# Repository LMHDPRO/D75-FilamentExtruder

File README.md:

<div align="center">

```
██████╗  ██████╗ ██╗   ██╗ ██████╗ ██╗      █████╗ ███████╗███╗███████╗
██╔══██╗██╔═══██╗██║   ██║██╔════╝ ██║     ██╔══██╗██╔════╝ ██║██╔════╝
██║  ██║██║   ██║██║   ██║██║  ███╗██║     ███████║███████╗╚██║███████╗
██║  ██║██║   ██║██║   ██║██║   ██║██║     ██╔══██║╚════██║ ██║╚════██║
██████╔╝╚██████╔╝╚██████╔╝╚██████╔╝███████╗██║  ██║███████║ ██║███████║
╚═════╝  ╚═════╝  ╚═════╝  ╚═════╝ ╚══════╝╚═╝  ╚═╝╚══════╝ ╚═╝╚══════╝
```

# Filament Extruder Controller

**ESP32 DualCore · FreeRTOS · PID Temperature · Dual TB6600**

*Reduce PP filament — 2.4 mm → 1.75 mm for 3D printing*

---

</div>

---

## ¿Qué es esto?

**Douglas75** es un controlador open-source para una extrusora de filamento, desarrollado originalmente en el marco de un **Practicum** universitario para reducir el diámetro de filamento fabricado artesanalmente. El diseño nació con polipropileno (PP) de **2.4 mm → 1.75 mm**, pero el sistema es compatible con cualquier tipo de filamento termoplástico que requiera un proceso de reducción controlada de diámetro.

El sistema corre en un **ESP32 con FreeRTOS dual-core** — un núcleo dedicado al control PID de temperatura y otro a la interfaz de usuario. Incluye un **panel de control Tkinter** para operación desde PC vía USB serial.

---

## Características

| | Función | Detalle |
|---|---|---|
| 🌡️ | Control temperatura | PID con NTC 100K genérico Ender3 (β = 3950) |
| 🔥 | Calefactor | MOSFET IRLZ44N, PWM 5 kHz vía LEDC |
| 💨 | Ventilador | MOSFET IRLZ44N, PWM proporcional AUTO o manual OFF |
| ⚙️ | Motores | 2× NEMA17 full-step, drivers TB6600, enable compartido |
| 🖥️ | LCD | I2C 20×4 @ 0x27, menú completo con encoder KY-040 |
| 💻 | GUI PC | Tkinter dark mode + gráfica temperatura en tiempo real |
| 🧵 | Estimación | Contador de filamento procesado (mm y gramos) |
| ⚡ | Arquitectura | FreeRTOS — Core 0: PID · Core 1: HMI |

---

## Hardware

### Bill of Materials (BOM)

| # | Categoría | Componente | Modelo / Especificación | Qty |
|:---:|---|---|---|:---:|
| 1 | 🧠 MCU | Microcontrolador | ESP32 Development Board | 1 |
| 2 | 🔥 Calefactor | Hotend completo | 40W 12V Ceramic Cartridge Heater + NTC 100K Thermistor | 1 |
| 3 | 🔩 Boquilla | Nozzle | MK8 0.4 mm Nozzle | 1 |
| 4 | ⚙️ Extrusión | Extrusor | Creality MK8 Extruder | 1 |
| 5 | ⚙️ Motor | Motor paso a paso | NEMA17 Stepper Motor | 2 |
| 6 | ⚙️ Driver | Driver motor | TB6600 Stepper Motor Driver | 2 |
| 7 | 🔧 Soporte | Montura motor | NEMA Motor Mount | 2 |
| 8 | 🖥️ Pantalla | Pantalla LCD | 20×4 LCD Screen I2C | 1 |
| 9 | 🎛️ Entrada | Encoder rotatorio | KY-040 Rotary Encoder | 1 |
| 10 | 🧵 Sensor | Sensor de filamento | Filament Runout Sensor | 1 |
| 11 | ⚡ Regulador | Regulador voltaje | L7805CV 5V Voltage Regulator (TO-220) | 1 |
| 12 | ⚡ MOSFET | MOSFET N-Channel | IRFL44N N-Channel MOSFET | 2 |
| 13 | 🔩 Rodamientos | Rodamiento | 608ZZ Bearing | 4 |
| 14 | 💨 Ventilador | Fan | 4010 Fan 12V | 1 |
| 15 | 🟫 PCB | Placa base | 15×15 cm Single-Sided Phenolic Board | 1 |
| 16 | 🔌 Conectores | Pin header | 36-pin Single Row Pin Header (2.54 mm) | 1 |
| 17 | 🔌 Conectores | Female header | 10-pin Female Header (2.54 mm) | 2 |
| 18 | 🔌 Conectores | Terminales | 2-Pin Green Screw Terminals | 6 |
| 19 | 🔋 Capacitores | Condensador electrolítico | 100 µF | 2 |
| 20 | 🔋 Capacitores | Condensador cerámico | 100 nF | 2 |
| 21 | 🔩 Tornillería | Tornillos Allen | M2, M3 & M4 Socket Head Screws (surtido) | — |

### Mapa de pines ESP32

| GPIO | Señal | Tipo |
|---|---|---|
| `18` | OUTA encoder (CLK) | Input interrupt |
| `19` | OUTB encoder (DT) | Input interrupt |
| `5` | SW encoder | Input PULLUP |
| `34` | Termistor NTC | ADC1_CH6 |
| `25` | MOSFET calefactor | PWM LEDC ch0 |
| `23` | MOSFET ventilador | PWM LEDC ch1 |
| `26` | STEP Motor 1 | Output |
| `27` | DIR Motor 1 | Output |
| `4` | STEP Motor 2 | Output |
| `2` | DIR Motor 2 | Output |
| `13` | EN_Driver | Output |
| `21` | SDA LCD | I2C |
| `22` | SCL LCD | I2C |

> ⚠️ **Pines prohibidos:** GPIO 0, 6–11 (flash interno), 12, 15

### Circuito divisor NTC

```
3.3V
 │
[4.7 KΩ]  ← R7 pull-up
 │
 ├──── GPIO34 ──────────────── net: Thermistor_GPIO34
 │
 ├──── 100 nF cerámico  ┐ en paralelo
 ├──── 10 µF electrolítico ┘
 │
[NTC 100K]  ← cable vía J3 terminal block
 │
GND
```

### Circuito calefactor

```
GPIO25 ──[10 Ω]──→ Gate IRLZ44N
                    Drain  → Calefactor DC 12V (−)
                    Source → GND

[10 KΩ] entre Gate y GND   ← pull-down, seguro durante boot
LED + [1.8 KΩ] en paralelo ← indicador visual de activación
```

### Alimentación dual USB + 12V

```
12V (fuente principal)
 ├── Buck LM2596 → 5V → VIN ESP32
 ├── TB6600 VMOT  (+ condensador 100 µF entre VMOT y GND)
 └── Calefactor DC (vía MOSFET)

USB-C ESP32 → PC  (serial Tkinter GUI)
✓ Coexistencia segura — diodo Schottky en DevKit aísla USB de VIN
```

---

## Menú LCD

```
ARRANQUE
  └── Splash 2s
        └── MENÚ PRINCIPAL
              ├── ► PRE-CALENTAR ──→ Calienta a 150 °C
              │                       Barra de progreso
              │                       Auto-arranca al llegar
              └── ► CONFIGURAR
                    ├── VELOCIDAD DRV 1   (0–300 RPM, paso 10)
                    ├── VELOCIDAD DRV 2   (0–300 RPM, paso 10)
                    ├── TEMPERATURA       (20–260 °C, paso 1)
                    └── VENTILADOR        (AUTO / OFF)

PANTALLA CORRIENDO:
  ┌────────────────────┐
  │ T:160.5C  SP:160C  │
  │ D1:100RPM D2:100RP │
  │ PWM:127   FAN:AUTO │
  │ CORRIENDO Lng=STOP │
  └────────────────────┘
```

**Controles encoder KY-040:**

| Acción | Función |
|---|---|
| Girar | Navegar menú / cambiar valor |
| Presión corta | Seleccionar / confirmar |
| Presión larga >700 ms | Volver / STOP de emergencia |

---

## Protocolo Serial

**115200 baud, 8N1**

### ESP32 → PC (cada 100 ms)

```
T:160.5,S:160,D1:100,D2:100,P:127,F:64,RUN:1
```

| Campo | Descripción |
|---|---|
| `T` | Temperatura real (°C) — o `ERR` si falla el sensor |
| `S` | Setpoint temperatura |
| `D1` / `D2` | RPM motores 1 y 2 |
| `P` | PWM calefactor (0–255) |
| `F` | PWM ventilador (0–255) |
| `RUN` | Estado extrusión `0`/`1` |

### PC → ESP32

| Comando | Descripción |
|---|---|
| `ST:165` | Cambiar setpoint temperatura |
| `SD1:100` | Cambiar RPM Motor 1 |
| `SD2:120` | Cambiar RPM Motor 2 |
| `SF:1` / `SF:0` | Ventilador AUTO / OFF |
| `RUN` | Iniciar extrusión |
| `STOP` | Detener extrusión |
| `JOG1:1` / `JOG1:0` | Motor 1 manual ON/OFF |
| `JOG2:1` / `JOG2:0` | Motor 2 manual ON/OFF |
| `EN:1` / `EN:0` | Habilitar / deshabilitar ambos TB6600 |

---

## Instalación

### Firmware ESP32

**1. Instalar PlatformIO:**

Instala la extensión [PlatformIO IDE](https://platformio.org/install/ide?install=vscode) para VS Code.

**2. Clonar y abrir el proyecto:**

```bash
git clone https://github.com/LMHDPRO/D75-FilamentExtruder.git
cd D75-FilamentExtruder
code .   # abrir en VS Code con PlatformIO
```

**3. Las dependencias se instalan automáticamente** desde `platformio.ini`:

```ini
[env:esp32dev]
platform  = espressif32
board     = esp32dev
framework = arduino
lib_deps  =
    mathertel/RotaryEncoder
    br3ttb/PID
    waspinator/AccelStepper
    marcoschwartz/LiquidCrystal_I2C
```

**4. Subir el firmware:**

Botón **Upload** (→) en la barra de PlatformIO, o:

```bash
pio run --target upload
```

> Si no entra en modo flash automáticamente, mantén presionado el botón **BOOT** del DevKit mientras sube.

**5. Verificar en Serial Monitor (115200 baud):**

```
T:25.3,S:160,D1:100,D2:100,P:0,F:0,RUN:0   ✓ Sensor OK
T:ERR,S:0,D1:0,D2:0,P:0,F:0,RUN:0          ✗ Revisar NTC o divisor
```

### GUI Python

```bash
pip install pyserial matplotlib
python extrusora_gui.py
```

---

## Arquitectura de software

```
ESP32 — FreeRTOS DualCore
│
├── Core 0  [prioridad 2]  taskPID
│    ├── Leer NTC (promedio 8 muestras)
│    ├── Calcular PID
│    ├── Escribir LEDC calefactor (0–255)
│    ├── Calcular PWM ventilador proporcional
│    └── Enviar telemetría serial cada 100 ms
│
└── Core 1  [prioridad 1]  taskHMI
     ├── Encoder KY-040 via interrupciones
     ├── Máquina de estados LCD (6 estados)
     ├── AccelStepper Motor 1 + Motor 2
     └── Parser comandos serial desde PC

Variables compartidas → protegidas con portMUX_TYPE
```

---

## Calibración

### Temperatura no coincide con la real

Cambiar `NTC_BETA` en `extrusora_esp32.ino`:

| Termistor | β |
|---|---|
| Genérico impresoras 3D (este proyecto) | **3950** |
| Semitec 104GT-2 | 4267 |
| EPCOS B57560G | 3988 |
| Marlin tabla 1 | 4388 |

### Motor gira al revés

```cpp
#define MOTOR_DIR  -1   →   #define MOTOR_DIR  1
```

### Estimación de filamento

Medir el diámetro del rodillo de arrastre con un vernier y actualizar en `extrusora_gui.py`:

```python
DRIVE_DIAM_MM = 11.0   # ← reemplazar con medición real
```

---

## Estructura del repositorio

```
D75-FilamentExtruder/
 ├── firmware/
 │    └── extrusora_esp32.ino      ← código ESP32
 ├── software/
 │    └── extrusora_gui.py         ← panel de control PC
 ├── hardware/
 │    ├── CircuitoESP32.kicad_sch  ← esquemático KiCad
 │    └── CircuitoESP32.kicad_pcb  ← PCB KiCad
 └── README.md
```

---

## Créditos

- [RotaryEncoder](https://github.com/mathertel/RotaryEncoder) — Matthias Hertel
- [Arduino PID Library](https://github.com/br3ttb/Arduino-PID-Library) — Brett Beauregard
- [AccelStepper](https://www.airspayce.com/mikem/arduino/AccelStepper/) — Mike McCauley
- [LiquidCrystal_I2C](https://github.com/marcoschwartz/LiquidCrystal_I2C) — Frank de Brabander

---

## Equipo

<div align="center">

*Proyecto desarrollado en la* **Universidad Anáhuac Mayab** *— Mérida, Yucatán*

<br>

| | Nombre | |
|:---:|:---|:---:|
| 🧑‍💻 | **Skyler Schenck** |  |
| 🧑‍💻 | **Darian Cuellar** |  |
| 🧑‍💻 | **José Pardiñaz** |  |
| 🧑‍💻 | **Douglas Fuentes** |  |
| 🧑‍🔬 | **Gerardo Alonzo** |  |
| 🧑‍🔬 | **Andrés Oliva** |  |

<br>

</div>

---

## Apoya el proyecto

Este proyecto es **open-source bajo licencia MIT** — puedes usarlo, modificarlo y distribuirlo libremente. Si te fue útil y quieres apoyar al creador, puedes conseguir los archivos 3D del modelo físico de la extrusora en Cults3D a precio libre:

<div align="center">

*Los archivos de código son y serán siempre gratuitos. El modelo 3D está disponible en Cults a precio libre — cualquier contribución es bienvenida y apoya el desarrollo continuo.*

</div>

---

## Licencia

MIT License — úsalo, modifícalo y distribúyelo libremente.

---

<div align="center">
<sub>Douglas75 Project · ESP32_Experimental · Made with ☕ in Mérida, MX</sub>
</div>

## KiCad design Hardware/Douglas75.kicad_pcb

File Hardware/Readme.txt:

KICAD 9.0

CREATED & DESIGNED BY JOSÉ PARDIÑAZ AND DOUGLAS FUENTES :)

V2. DARIAN CUELLAR

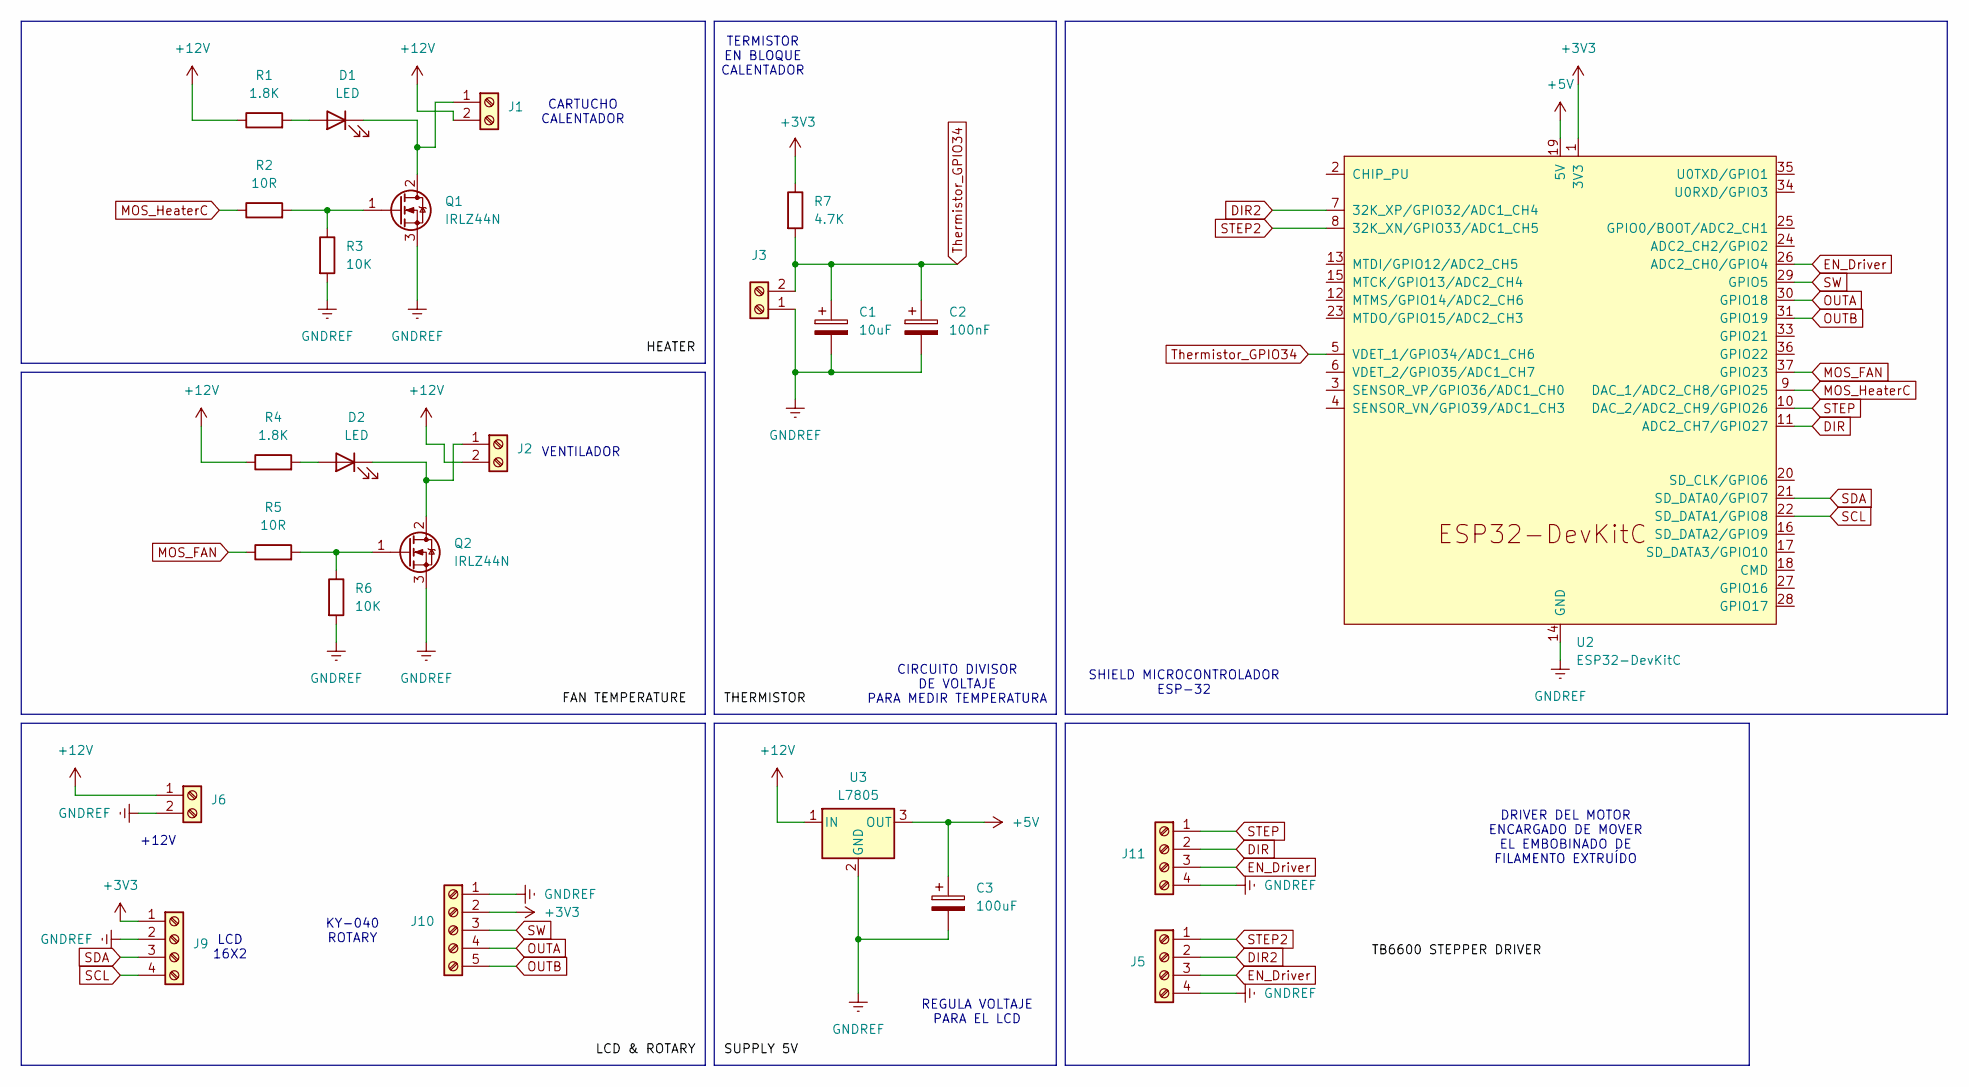
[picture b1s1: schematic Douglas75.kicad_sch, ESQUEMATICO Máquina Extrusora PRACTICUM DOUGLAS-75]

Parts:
C1: 10uF; CP_Radial_D4.0mm_P2.00mm
C2: 100nF; CP_Radial_D4.0mm_P2.00mm
C3: 100uF; CP_Radial_D5.0mm_P2.00mm
D1, D2: LED; LED_D5.0mm
J1, J2, J3, J6: TerminalBlock_Phoenix_MKDS-1,5-2-5.08_1x02_P5.08mm_Horizont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
J5, J9, J11: TerminalBlock_Phoenix_MKDS-1,5-4-5.08_1x04_P5.08mm_Horizont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
J10: TerminalBlock_Phoenix_MKDS-1,5-5-5.08_1x05_P5.08mm_Horizont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
Q1, Q2: IRLZ44N; TO-220-3_Vertical
R1, R4: 1.8K; R_Axial_DIN0309_L9.0mm_D3.2mm_P15.24mm_Horizontal
R2, R5: 10R; R_Axial_DIN0309_L9.0mm_D3.2mm_P15.24mm_Horizontal
R3, R6: 10K; R_Axial_DIN0309_L9.0mm_D3.2mm_P15.24mm_Horizontal
R7: 4.7K; R_Axial_DIN0309_L9.0mm_D3.2mm_P15.24mm_Horizontal
U2: ESP32-DevKitC
U3: L7805; TO-220-3_Vertical

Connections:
+3V3: J9.1, J10.2, R7.1, U2.1 (3V3)
+5V: C3.1, U2.19 (5V), U3.3 (OUT)
+12V: J1.2, J2.2, J6.1, R1.1, R4.1, U3.1 (IN)
DIR: J11.2, U2.11 (ADC2_CH7/GPIO27)
DIR2: J5.2, U2.7 (32K_XP/GPIO32/ADC1_CH4)
EN_Driver: J5.3, J11.3, U2.26 (ADC2_CH0/GPIO4)
GNDREF: C1.2, C2.2, C3.2, J3.1, J5.4, J6.2, J9.2, J10.1, J11.4, Q1.3 (S), Q2.3 (S), R3.2, R6.2, U2.14 (GND), U2.32 (GND), U2.38 (GND), U3.2 (GND)
MOS_FAN: R5.1, U2.37 (GPIO23)
MOS_HeaterC: R2.1, U2.9 (DAC_1/ADC2_CH8/GPIO25)
unnamed: D1.2 (A), R1.2
unnamed: D1.1 (K), J1.1, Q1.2 (D)
unnamed: D2.2 (A), R4.2
unnamed: D2.1 (K), J2.1, Q2.2 (D)
unnamed: Q1.1 (G), R2.2, R3.1
unnamed: Q2.1 (G), R5.2, R6.1
OUTA: J10.4, U2.30 (GPIO18)
OUTB: J10.5, U2.31 (GPIO19)
SCL: J9.4, U2.22 (SD_DATA1/GPIO8)
SDA: J9.3, U2.21 (SD_DATA0/GPIO7)
STEP: J11.1, U2.10 (DAC_2/ADC2_CH9/GPIO26)
STEP2: J5.1, U2.8 (32K_XN/GPIO33/ADC1_CH5)
SW: J10.3, U2.29 (GPIO5)
Thermistor_GPIO34: C1.1, C2.1, J3.2, R7.2, U2.5 (VDET_1/GPIO34/ADC1_CH6)

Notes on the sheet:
VENTILADOR
DRIVER DEL MOTOR ENCARGADO DE MOVER EL EMBOBINADO DE FILAMENTO EXTRUÍDO
SHIELD MICROCONTROLADOR ESP-32
KY-040 ROTARY
CIRCUITO DIVISOR DE VOLTAJE PARA MEDIR TEMPERATURA
CARTUCHO CALENTADOR
TERMISTOR EN BLOQUE CALENTADOR
REGULA VOLTAJE PARA EL LCD
+12V
LCD 16X2

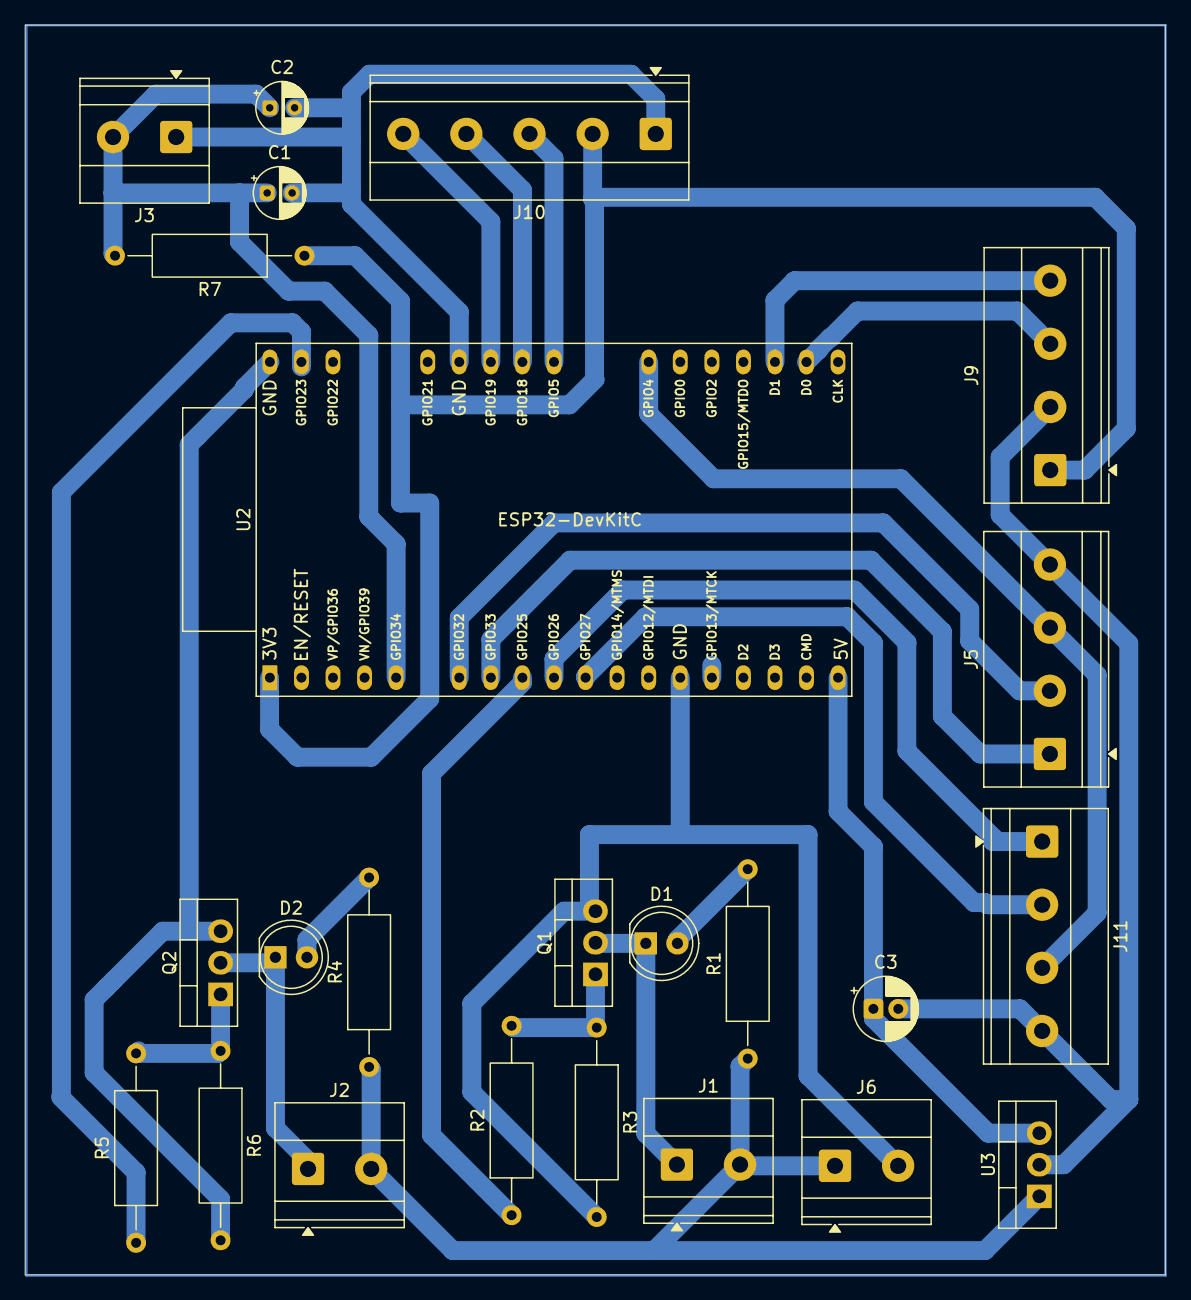
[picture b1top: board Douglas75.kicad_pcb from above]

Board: 2 copper layers, 91.8 x 100.6 mm, 24 parts (0 on the bottom side), 23 nets.

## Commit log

2025-02-26 Create LICENSE
2025-02-26 LICENSE
2026-03-18 Create Docs
2026-03-18 Rename Firmware_D75_ESP32_260225.ino to Firmware/Firmware_D75_Arduino_260225.ino
2026-03-18 Rename Firmware_D75_Arduino_2025.ino to Dou75_Firmware_Arduino_260225.ino
2026-03-18 Add new firmware file for Dou75 Arduino
2026-03-18 Add firmware for ESP32 DualCore extruder control
2026-03-18 Add Douglas75 GUI control panel code
    Initial commit of Douglas75 GUI control panel code.
2026-03-18 Rename Douglas75_GUI to Software/Douglas75_GUI
2026-03-18 Update Readme.txt with version and authors
2026-03-18 Revise README with project enhancements and credits
    Updated README to include new project details and features.
2026-03-18 Revise README with project details and support info
    Updated project description and bill of materials format. Added support information and modified contributor details.
2026-03-18 Refactor MotorCard class and improve layout

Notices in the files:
README.md:
License: MIT
